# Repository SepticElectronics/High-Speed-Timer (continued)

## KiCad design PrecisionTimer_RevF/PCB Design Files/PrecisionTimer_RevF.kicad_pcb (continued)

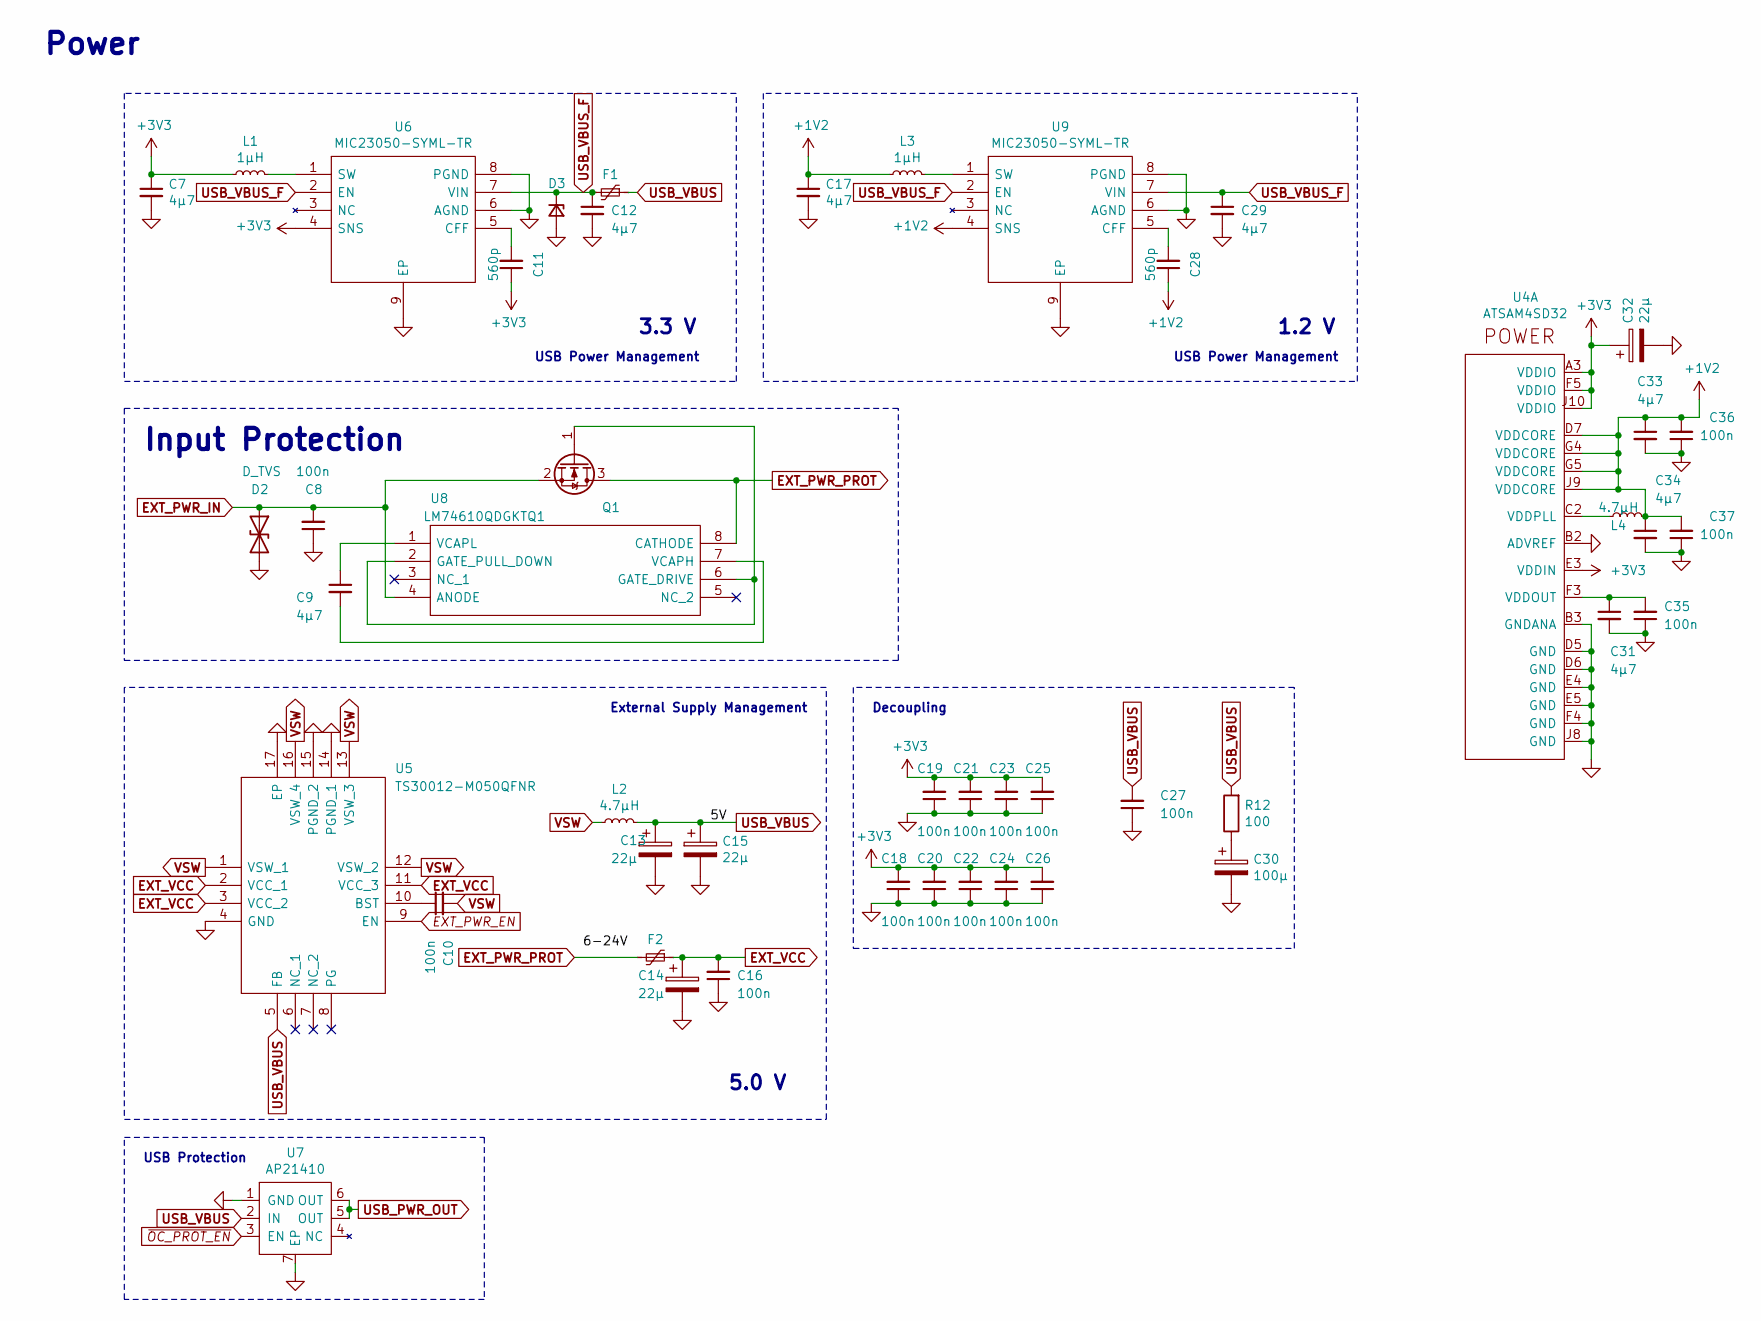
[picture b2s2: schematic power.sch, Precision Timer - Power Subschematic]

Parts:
C7, C9, C12, C17, C29, C31, C33, C34: 4µ7; C_0603_1608Metric
C8, C10, C16, C18, C19, C20, C21, C22, C23, C24, C25, C26, C27, C35, C36, C37: 100n; C_0603_1608Metric
C11, C28: 560p; C_0603_1608Metric
C13, C14, C15, C32: 22µ; C_0805_2012Metric
C30: 100µ; CP_Elec_5x5.4
D2: D_TVS; D_SMB
D3: D_Zener_Small; D_MiniMELF
F1, F2: Polyfuse_Small; Fuse_1206_3216Metric_Castellated
L1, L3: 1µH; L_0805_2012Metric
L2, L4: 4.7µH; L_0805_2012Metric
Q1: Q_NMOS_GSD; SOT-23
R12: 100; R_0805_2012Metric
U4: ATSAM4SD32; TFBGA-100_9.0x9.0mm_Layout10x10_P0.8mm
U5: TS30012-M050QFNR; QFN50P300X300X100-17N-D; Manufacturer_Part_Number TS30012-M050QFNR; Mouser Part Number 947-TS30012-M050QFNR
U6, U9: MIC23050-SYML-TR; SON50P200X200X90-9N; Manufacturer_Part_Number MIC23050-SYML-TR; Mouser Part Number 998-MIC23050-SYMLTR
U7: AP21410; DFN-6-1EP_2x1.8mm_P0.5mm_EP1.2x1.6mm
U8: LM74610QDGKTQ1; SOP65P490X110-8N; Manufacturer_Part_Number LM74610QDGKTQ1; Mouser Part Number 595-LM74610QDGKTQ1

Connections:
+1V2: C17.1, C28.1, C33.1, C34.1, C36.2, C37.2, L3.1, L4.2, U4.D7 (VDDCORE), U4.G4 (VDDCORE), U4.G5 (VDDCORE), U4.J9 (VDDCORE), U9.4 (SNS); also elsewhere on the board
+3V3: C7.1, C11.1, C18.2, C19.2, C20.2, C21.2, C22.2, C23.2, C24.2, C25.2, C26.2, C32.1, L1.1, U4.A3 (VDDIO), U4.E3 (VDDIN), U4.F5 (VDDIO), U4.J10 (VDDIO), U6.4 (SNS); also elsewhere on the board
EXT_PWR_EN: U5.9 (EN); also elsewhere on the board
EXT_PWR_IN: C8.2, D2.1 (A1), Q1.2 (S), U8.4 (ANODE); also elsewhere on the board
EXT_PWR_PROT: F2.2, Q1.3 (D), U8.8 (CATHODE); also elsewhere on the board
EXT_VCC: C14.1, C16.2, F2.1, U5.2 (VCC_1), U5.3 (VCC_2), U5.11 (VCC_3); also elsewhere on the board
GND: C7.2, C8.1, C12.2, C13.2, C14.2, C15.2, C16.1, C17.2, C18.1, C19.1, C20.1, C21.1, C22.1, C23.1, C24.1, C25.1, C26.1, C27.1, C29.2, C30.2, C31.2, C32.2, C33.2, C34.2, C35.1, C36.1, C37.1, D2.2 (A2), D3.2 (A), U4.B2 (ADVREF), U4.B3 (GNDANA), U4.D5 (GND), U4.D6 (GND), U4.E4 (GND), U4.E5 (GND), U4.F4 (GND), U4.J8 (GND), U5.4 (GND), U5.14 (PGND_1), U5.15 (PGND_2), U5.17 (EP), U6.6 (AGND), U6.8 (PGND), U6.9 (EP), U7.1 (GND), U7.7 (EP), U9.6 (AGND), U9.8 (PGND), U9.9 (EP); also elsewhere on the board
unnamed: C9.1, U8.1 (VCAPL)
unnamed: C9.2, U8.7 (VCAPH)
unnamed: C10.1, U5.10 (BST)
unnamed: C11.2, U6.5 (CFF)
unnamed: C28.2, U9.5 (CFF)
unnamed: C30.1, R12.1
unnamed: C31.1, C35.2, U4.F3 (VDDOUT)
unnamed: L1.2, U6.1 (SW)
unnamed: L3.2, U9.1 (SW)
unnamed: L4.1, U4.C2 (VDDPLL)
unnamed: Q1.1 (G), U8.2 (GATE_PULL_DOWN), U8.6 (GATE_DRIVE)
USB_PWR_OUT: U7.5 (OUT), U7.6 (OUT); also elsewhere on the board
USB_VBUS: C13.1, C15.1, C27.2, F1.1, L2.2, R12.2, U5.5 (FB), U7.2 (IN); also elsewhere on the board
USB_VBUS_F: C12.1, C29.1, D3.1 (K), F1.2, U6.2 (EN), U6.7 (VIN), U9.2 (EN), U9.7 (VIN); also elsewhere on the board
VSW: C10.2, L2.1, U5.1 (VSW_1), U5.12 (VSW_2), U5.13 (VSW_3), U5.16 (VSW_4); also elsewhere on the board
~OC_PROT_EN: U7.3 (EN); also elsewhere on the board

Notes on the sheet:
USB Power Management
Decoupling
External Supply Management
Power
USB Protection
3.3 V
1.2 V
5.0 V
Input Protection

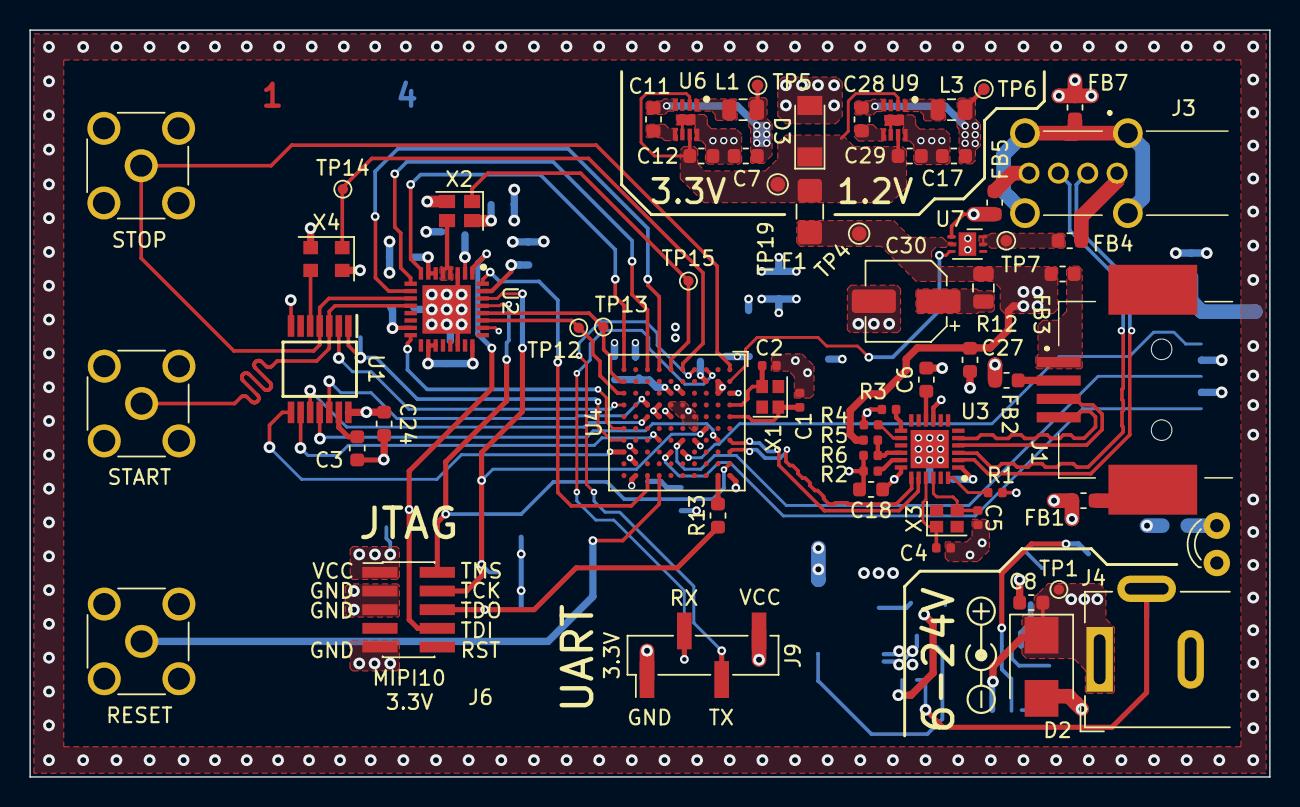
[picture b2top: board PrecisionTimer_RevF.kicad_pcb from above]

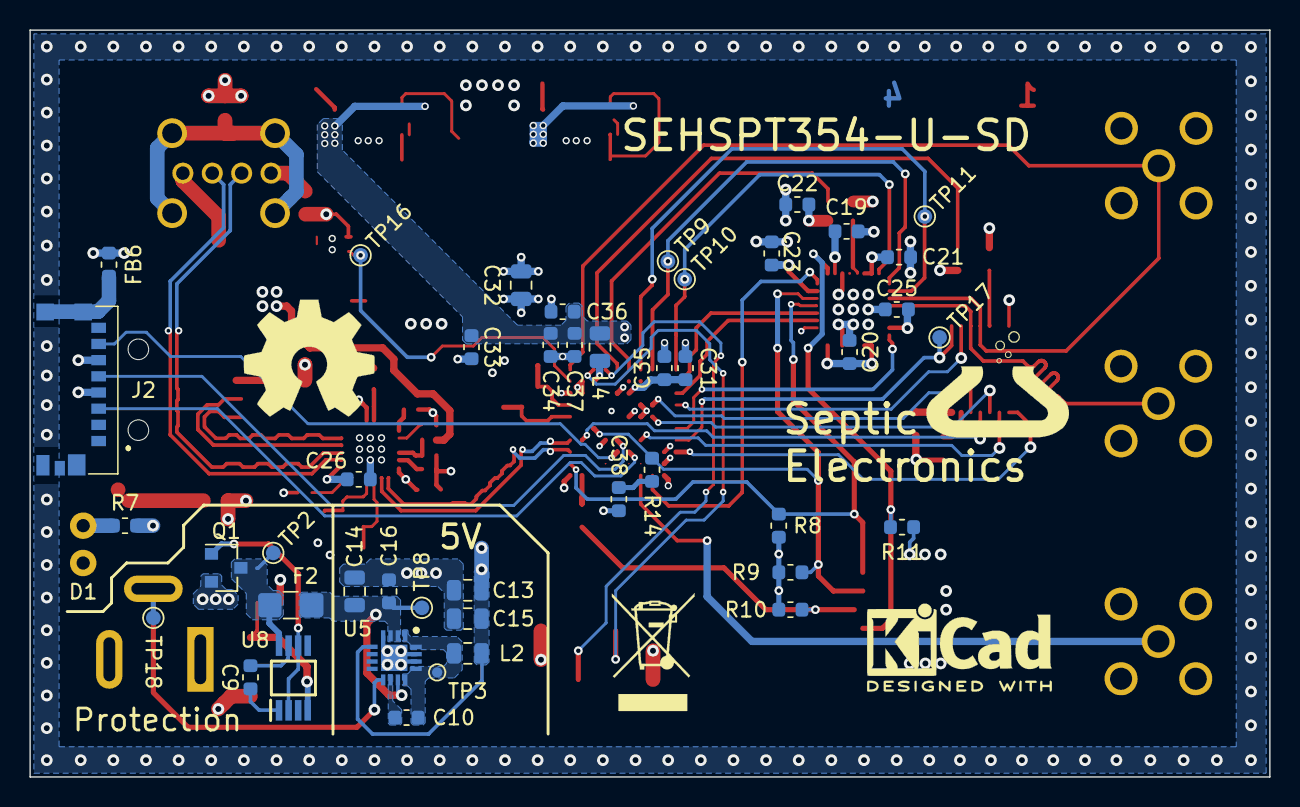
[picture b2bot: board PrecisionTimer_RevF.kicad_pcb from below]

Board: 4 copper layers, 84.3 x 50.8 mm, 110 parts (44 on the bottom side), 80 nets.

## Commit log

2020-07-25 Rename PrecisionTimer_RevF/PrecisionTimer_RevF-cache.lib to PrecisionTimer_RevF/PCB Design Files/PrecisionTimer_RevF-cache.lib
2020-07-25 Rename PrecisionTimer_RevF/PrecisionTimer_RevF.kicad_pcb to PrecisionTimer_RevF/PCB Design Files/PrecisionTimer_RevF.kicad_pcb
2020-07-25 Rename PrecisionTimer_RevF/PrecisionTimer_RevF.kicad_pcb-bak to PrecisionTimer_RevF/PCB Design Files/PrecisionTimer_RevF.kicad_pcb-bak
2020-07-25 Rename PrecisionTimer_RevF/PrecisionTimer_RevF.net to PrecisionTimer_RevF/PCB Design Files/PrecisionTimer_RevF.net
2020-07-25 Rename PrecisionTimer_RevF/PrecisionTimer_RevF.pro to PrecisionTimer_RevF/PCB Design Files/PrecisionTimer_RevF.pro
2020-07-25 Rename PrecisionTimer_RevF/PrecisionTimer_RevF.sch-bak to PrecisionTimer_RevF/PCB Design Files/PrecisionTimer_RevF.sch-bak
2020-07-25 Rename PrecisionTimer_RevF/PrecisionTimer_RevF_back.kicad_pcb to PrecisionTimer_RevF/PCB Design Files/PrecisionTimer_RevF_back.kicad_pcb
2020-07-25 Rename PrecisionTimer_RevF/PrecisionTimer_RevF_back2.kicad_pcb to PrecisionTimer_RevF/PCB Design Files/PrecisionTimer_RevF_back2.kicad_pcb
2020-07-25 Rename PrecisionTimer_RevF/power.sch to PrecisionTimer_RevF/PCB Design Files/power.sch
2020-07-25 Rename PrecisionTimer_RevF/power.sch-bak to PrecisionTimer_RevF/PCB Design Files/power.sch-bak
2020-07-25 Update issue templates
